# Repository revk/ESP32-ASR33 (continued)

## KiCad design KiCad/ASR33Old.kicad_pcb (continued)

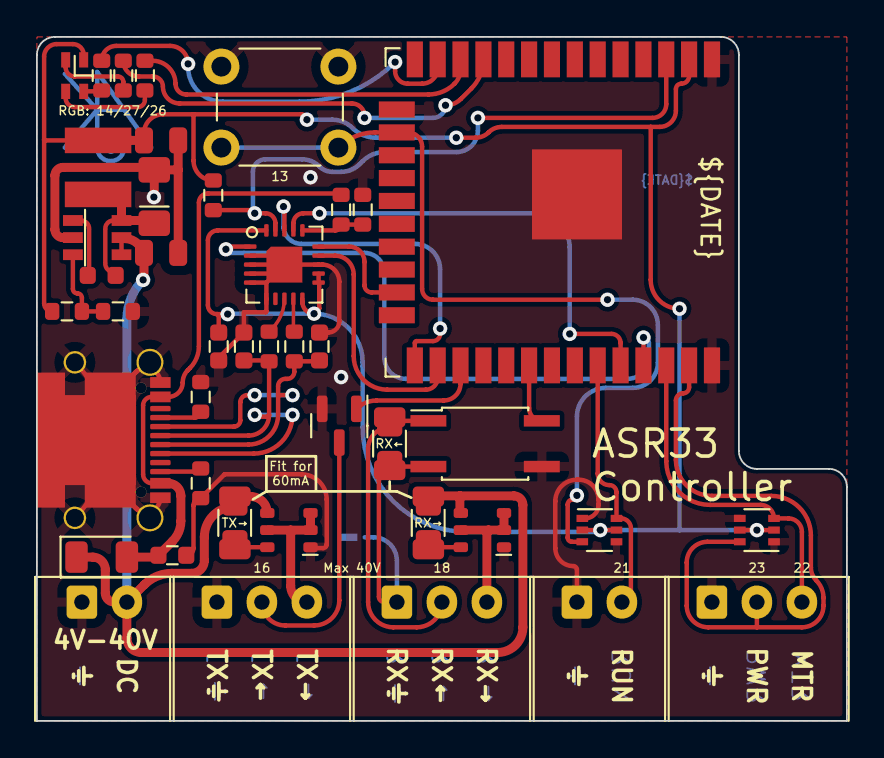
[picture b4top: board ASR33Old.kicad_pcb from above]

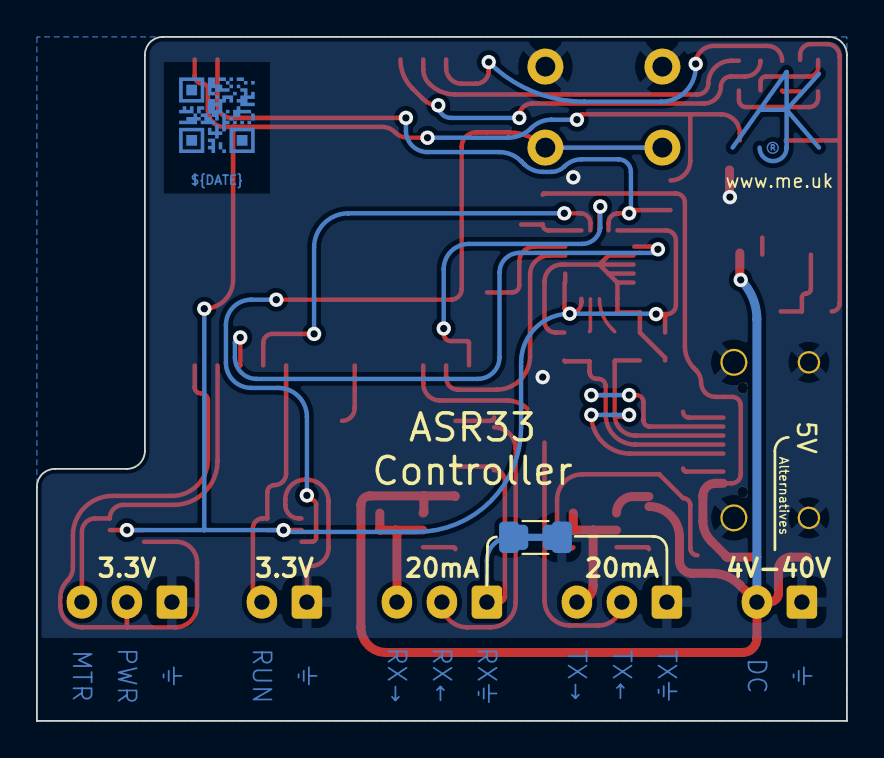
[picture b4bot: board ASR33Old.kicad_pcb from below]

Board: 2 copper layers, 45.0 x 38.0 mm, 45 parts (3 on the bottom side), 37 nets.

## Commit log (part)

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2020-12-28 Cave only mode
2020-12-28 The library sets strings to empty string so no need for null check
2020-12-28 Tweak GPIO and defaults
2020-12-30 Change defaults
2020-12-31 Some extra controls
2020-12-31 Instructions
2020-12-31 WRU logic
2021-01-01 Tweak
2021-01-01 Added answerback drum
2021-01-02 Suppress WRU from punching
2021-01-02 xoff separate from echo control
2021-01-02 Tidy
2021-01-03 on/off event
2021-01-03 Timing
2021-01-03 Tape read
2021-01-03 8 bit read
2021-01-03 start of line
2021-01-03 AS was
2021-01-06 Fix broken wrapping when unicode chars
2021-01-09 Twitter handles on command line
2021-01-12 Minor tweak
2021-02-18 Parity on adventure came
2021-04-11 More options to invert pins
2021-04-11 Changed defaults to use the OTA board
2021-04-11 Library update
2021-04-11 Use OTA board
2021-04-11 Tweaks
2021-04-11 Changed default
2021-04-11 Typo
2021-04-11 V3 OTA
2021-04-13 Tweaks for new OTA board
2021-04-13 Note
2021-04-13 Correct pin values
2021-06-06 JSON ALL THE THINGS!
2021-06-06 Memory leak
2021-06-06 JSON
2021-07-09 New RevK library
2021-07-13 New library
2021-09-10 Latest generic board
2021-10-08 Cmake
2021-12-08 line/bell
2022-01-23 New dedicated ASR33 PCB
2022-01-23 Notes
2022-01-23 Ignore
2022-01-24 Reworked
2022-01-24 New PCB
2022-01-24 Tweak, added button
2022-01-24 Tweaked PCB
2022-01-24 Correct pos for regulator
2022-01-26 Gold lettering
2022-01-27 Tidy GPIO naming and invert logic
2022-01-27 Tidy settings for GPIO
2022-01-27 Tidy up a bit
2022-01-27 Crash
2022-01-27 Ooops
2022-01-27 format
2022-01-27 TCP port accept
2022-01-27 TCP port
2022-01-27 Reporting
2022-01-28 pull up etc
2022-01-28 Reworkd tx/rx
2022-01-28 Reworked PCB and manuals
2022-01-28 Added network on Tx, same as FS-2 send circuit.
2022-01-28 Image
2022-01-29 Complete re-work with more connectors.
2022-01-29 Diode
2022-01-29 Read for when 3D case works again
2022-01-29 More tinkering
2022-01-29 Tinker
2022-01-29 Fix resistor values on LED
2022-01-29 Round corners
2022-01-30 Label GPIOs on silkscreen
2022-01-30 60mA
2022-01-30 More on 60mA
2022-01-30 Tidy silk screen
2022-01-30 Better 60mA documentaion
2022-01-30 Document voltages
2022-01-30 Voltages
2022-01-30 Tweak tracks
2022-01-31 Baud, databits, and stop bits
2022-01-31 Started on 3D case
2022-01-31 Min 110
2022-01-31 Started on 3D
2022-01-31 Clarify voltages and 60mA working
2022-02-01 Starting code for soft uart
2022-02-01 Started on soft uart code
2022-02-01 Comment
2022-02-01 Started soft uart option
2022-02-01 Soft UART Tx seems to be working
2022-02-01 TX break
2022-02-01 Soft UART Rx
2022-02-01 Soft UART working well including break send and detect
2022-02-01 Baud rate controls
2022-02-01 Updated for new soft UART options
2022-02-05 Bad stop bit does not clock in byte
2022-02-05 Close TCP on power off and on BREAK
2022-02-05 Changed defaults for new board
2022-02-05 APGPIO default
2022-02-05 Fix default
2022-02-05 Default rxpu is true
2022-02-05 Blink defgaults
2022-02-05 Documentation
2022-02-05 Hayes
2022-02-05 Hayes detect
2022-02-05 Break count bits
2022-02-05 Started on prompt
2022-02-05 Prompt OK with IP
2022-02-05 Started on outgoing connect
2022-02-05 Making outgoing
2022-02-05 Cleaner
2022-02-05 Document outgoing and +++
2022-02-05 TCP socket is raw to teletype
2022-02-06 Reworked power control a lot
2022-02-06 CR gap
2022-02-06 Removed old pos/space logic
2022-02-06 Stats
2022-02-06 Manual
2022-02-06 Longer default
2022-02-07 No BREAK when off, shame
2022-02-07 BOM fix
2022-02-08 Various tidy of soft uart
2022-02-08 Power for break
2022-02-08 Silkscreenm
2022-02-08 Tidy up logic for initial settings
2022-02-08 Startd on LED and autoconnect
2022-02-08 More LED
2022-02-08 3D case initial try
2022-02-08 Tidy up for sending files
2022-02-08 Neater
2022-02-08 New 3D cases
2022-02-09 BREAK as RUN
2022-02-09 BREAK
2022-02-09 line was missing spaces
2022-02-09 Buggered up the tx
2022-02-09 Revert BREAK
2022-02-09 Don't try and connect when connected
2022-02-09 Game init
2022-02-20 Corrected VBUS/DC working, and moved some GPIO to avoid problematic startup strapping.
2022-02-20 Revised ports
2022-02-20 Revised GPIO defauls
2022-02-21 Suffix
2022-02-21 Make / defaults tidy
2022-02-22 FFS, missed 3.3V to FT231XQ
2022-02-23 Old ESP32-WROOM-32 based
2022-02-23 New PICO version
2022-02-23 New board
2022-02-23 Reinstated the GND link
2022-02-23 Tidy up
2022-02-24 Very minor tweak
2022-02-24 Tidy schematic
2022-03-11 Tidy 3D
2022-03-17 Resistors
2022-06-23 Tweak PCB layout
2022-12-31 v5.0 timer
2023-01-01 v5.0
2023-03-27 New Manuals in markdown and new PCB connectos
2023-03-27 Updated STL
2023-03-27 New image
2023-03-27 Link
2023-04-17 Issue
2023-04-17 Updated lib
2023-04-17 Legacy
2023-06-11 Production files
2023-06-11 Added programming header for when not using USB data
2023-06-11 Rework for 5 pin header instead of USB/USART
2023-06-11 Images
2023-06-11 Non USB
2023-06-12 Purchase link
2023-06-13 checkpoint
2023-06-13 release
2023-06-15 Prog header
2023-06-17 Silk
2023-06-18 Tidy silk
2023-06-22 popt changes
2023-08-13 New layout with S3
2023-08-19 New reg
2023-12-29 backoff
2023-12-29 reconnect
2024-01-19 iTidy
2024-01-26 Clean up PCB
2024-02-10 betarelease
2024-03-02 Beta
2024-03-17 Pos file
2024-08-03 Update for ESP32 and latest boards with WS2812 LED
2024-08-03 time in s
2024-08-24 Clean up commits
2024-08-24 Tidy for S1
2024-08-24 Corrected stop bits
2024-08-25 Clean up rx soft uart slightly
2024-09-02 Consistent timing settings and more controls
2024-09-24 Web interface
2024-09-24 Parity checks
2024-09-26 Interactive web page Allow pwr not set for xon
2024-10-02 Rx tevel (test)
2024-10-02 Reporting BREAK
2025-01-13 New settings and beta
2025-01-13 New images
2025-01-14 Production
2025-01-15 New artwork
2025-01-19 Footprint update
2025-01-23 PCB Update
2025-01-27 New defaults
2025-01-31 Image and new tc2030
2025-09-20 New casework
